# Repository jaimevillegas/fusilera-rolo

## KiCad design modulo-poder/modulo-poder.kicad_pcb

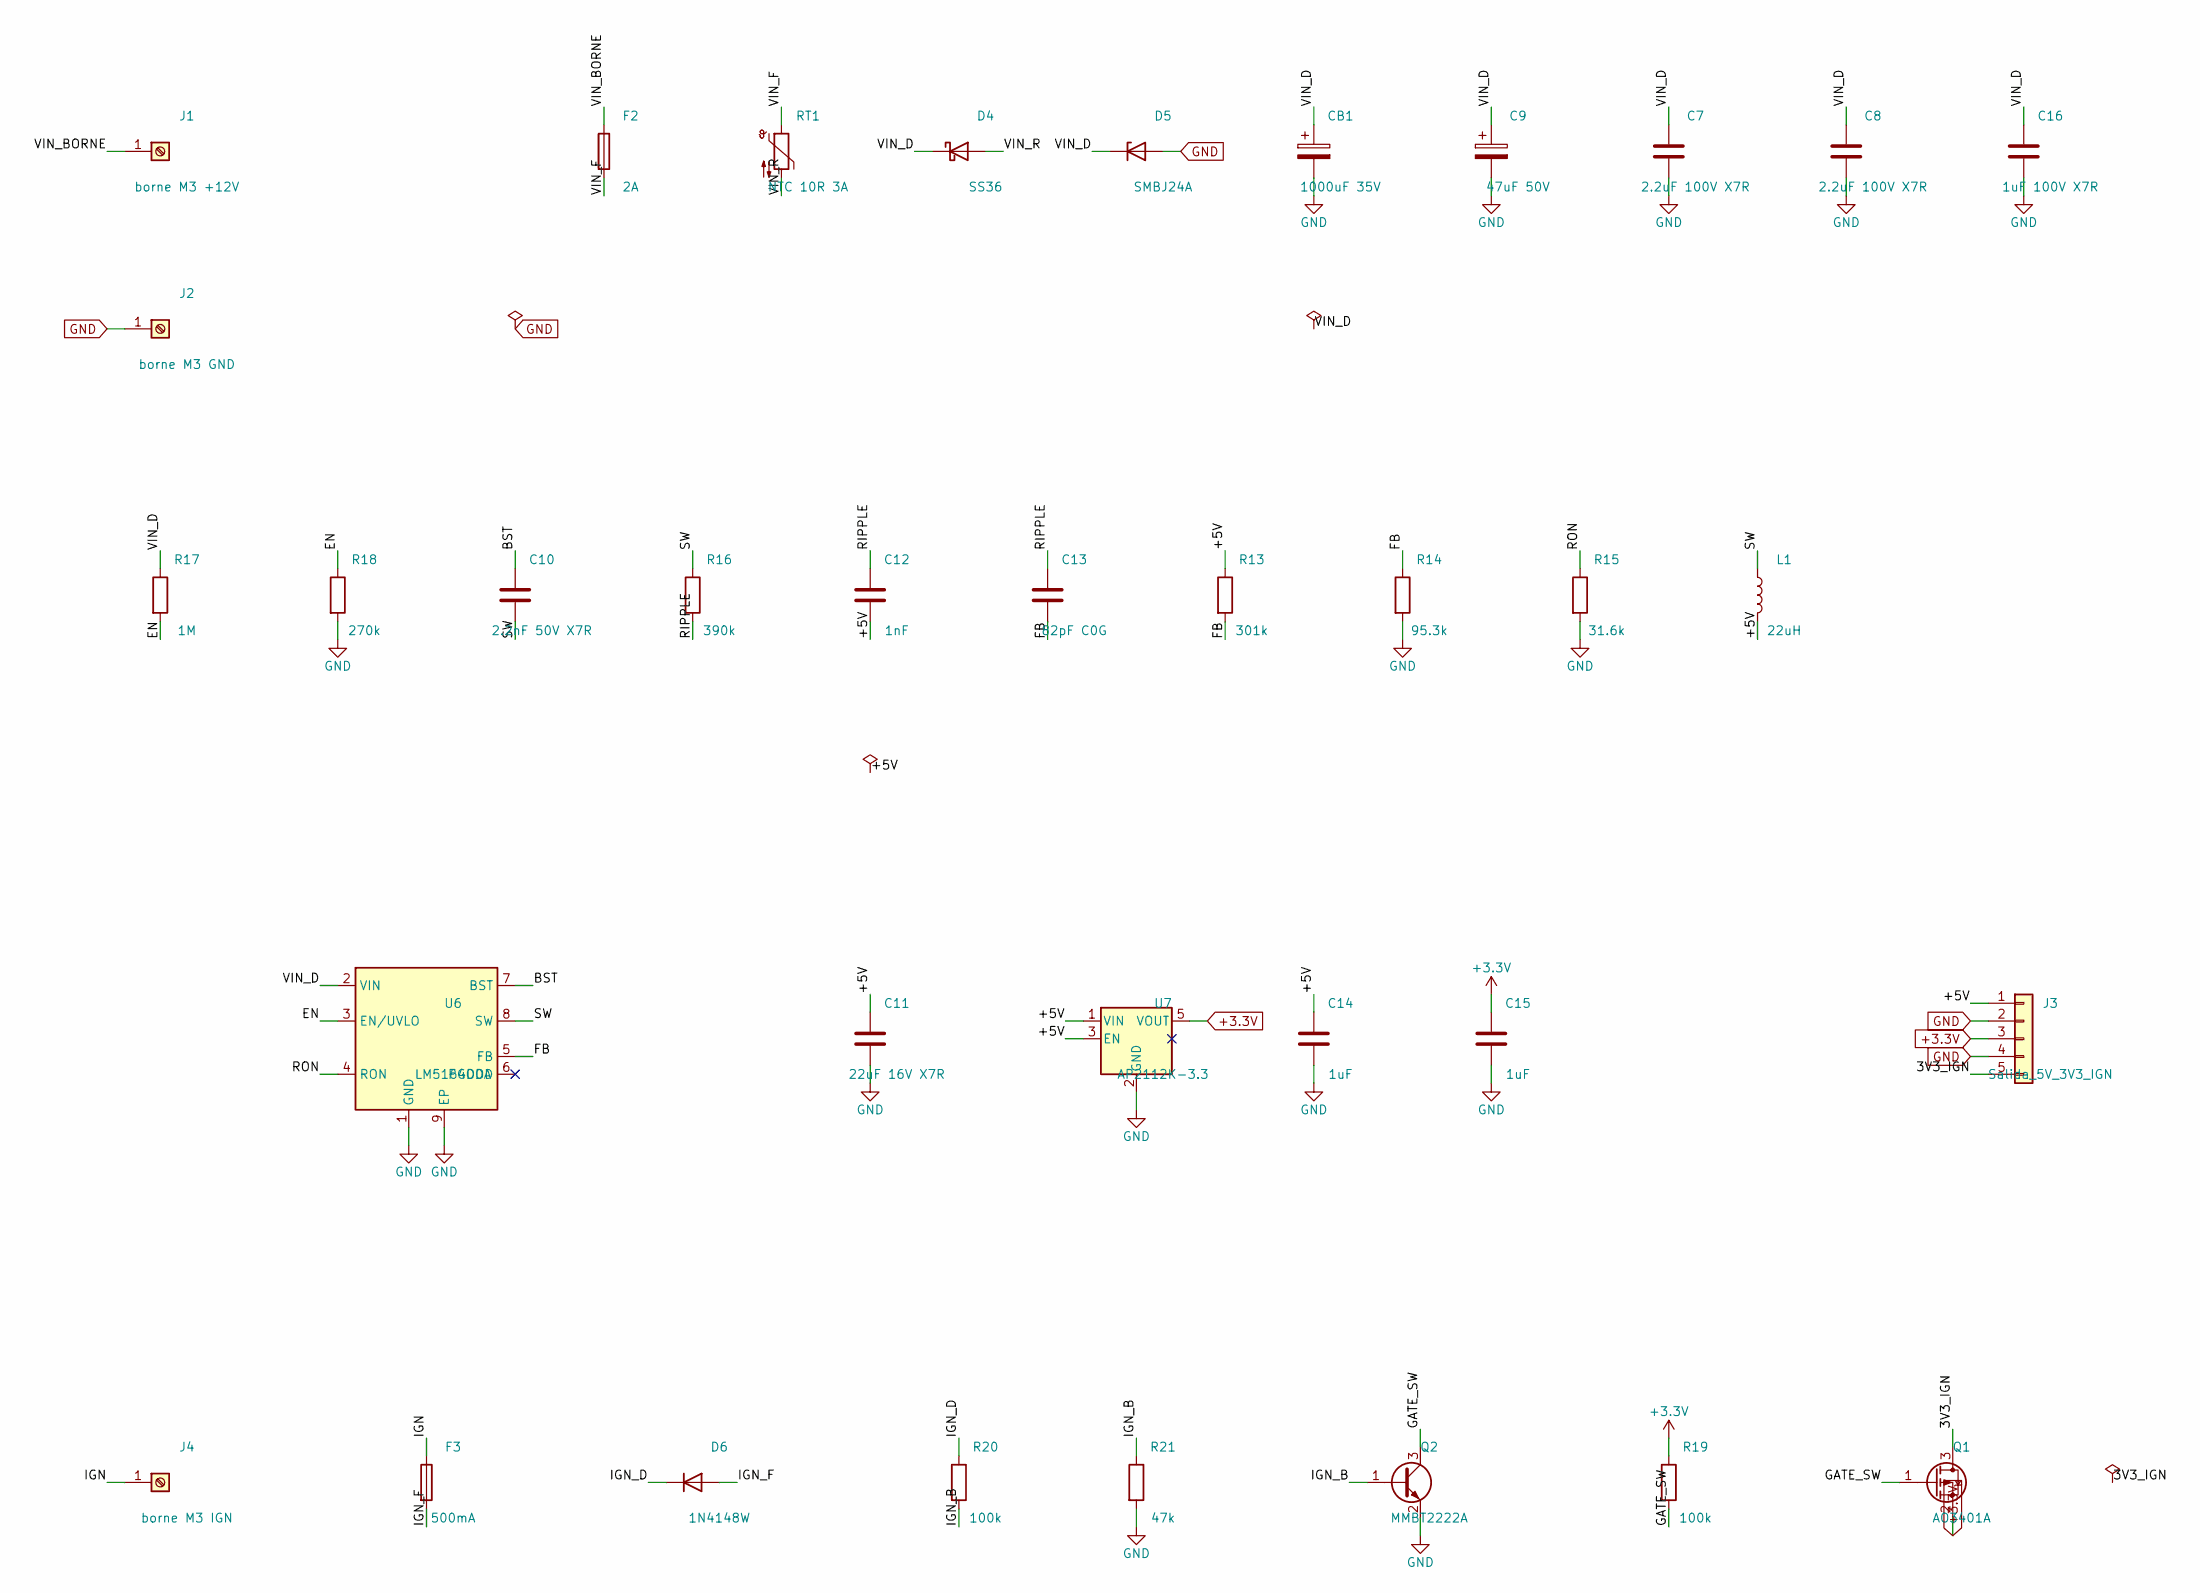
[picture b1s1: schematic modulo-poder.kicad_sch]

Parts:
C7, C8: 2.2uF 100V X7R; C_1210_3225Metric
C9: 47uF 50V; CP_Elec_8x10
C10: 2.2nF 50V X7R; C_0805_2012Metric
C11: 22uF 16V X7R; C_1206_3216Metric
C12: 1nF; C_0805_2012Metric
C13: 82pF C0G; C_0805_2012Metric
C14, C15: 1uF; C_0805_2012Metric
C16: 1uF 100V X7R; C_0805_2012Metric
CB1: 1000uF 35V; CP_Radial_D10.0mm_P5.00mm
D4: SS36; D_SMB
D5: SMBJ24A; D_SMB
D6: 1N4148W; D_SOD-123
F2: 2A; Fuse_1206_3216Metric
F3: 500mA; Fuse_1206_3216Metric
J1: borne M3 +12V; MountingHole_3.2mm_M3_Pad
J2: borne M3 GND; MountingHole_3.2mm_M3_Pad
J3: Salida_5V_3V3_IGN; JST_XH_B5B-XH-A_1x05_P2.50mm_Vertical
J4: borne M3 IGN; MountingHole_3.2mm_M3_Pad
L1: 22uH; L_6.3x6.3_H3
Q1: AO3401A; SOT-23
Q2: MMBT2222A; SOT-23
R13: 301k; R_0805_2012Metric
R14: 95.3k; R_0805_2012Metric
R15: 31.6k; R_0805_2012Metric
R16: 390k; R_0805_2012Metric
R17: 1M; R_0805_2012Metric
R18: 270k; R_0805_2012Metric
R19, R20: 100k; R_0805_2012Metric
R21: 47k; R_0805_2012Metric
RT1: NTC 10R 3A; RV_Disc_D9mm_W4.2mm_P5mm
U6: LM5164DDA; HSOP-8-1EP_3.9x4.9mm_P1.27mm_EP2.41x3.1mm
U7: AP2112K-3.3; SOT-23-5

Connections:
+3.3V: C15.1, J3.3, Q1.2 (S), R19.1, U7.5 (VOUT)
/3V3_IGN: J3.5, Q1.3 (D)
/+5V: C11.1, C12.2, C14.1, J3.1, L1.2, R13.1, U7.1 (VIN), U7.3 (EN)
/BST: C10.1, U6.7 (BST)
/EN: R17.2, R18.1, U6.3 (EN/UVLO)
/FB: C13.2, R13.2, R14.1, U6.5 (FB)
/GATE_SW: Q1.1 (G), Q2.3 (C), R19.2
/IGN: F3.1, J4.1; also elsewhere on the board
/IGN_B: Q2.1 (B), R20.2, R21.1
/IGN_D: D6.1 (K), R20.1
/IGN_F: D6.2 (A), F3.2
/RIPPLE: C12.1, C13.1, R16.2
/RON: R15.1, U6.4 (RON)
/SW: C10.2, L1.1, R16.1, U6.8 (SW)
/VIN_BORNE: F2.1, J1.1; also elsewhere on the board
/VIN_D: C7.1, C8.1, C9.1, C16.1, CB1.1, D4.1 (K), D5.1 (K), R17.1, U6.2 (VIN)
/VIN_F: F2.2, RT1.1
/VIN_R: D4.2 (A), RT1.2
GND: C7.2, C8.2, C9.2, C11.2, C14.2, C15.2, C16.2, CB1.2, D5.2 (A), J2.1, J3.2, J3.4, Q2.2 (E), R14.2, R15.2, R18.2, R21.2, U6.1 (GND), U6.9 (EP), U7.2 (GND); also elsewhere on the board

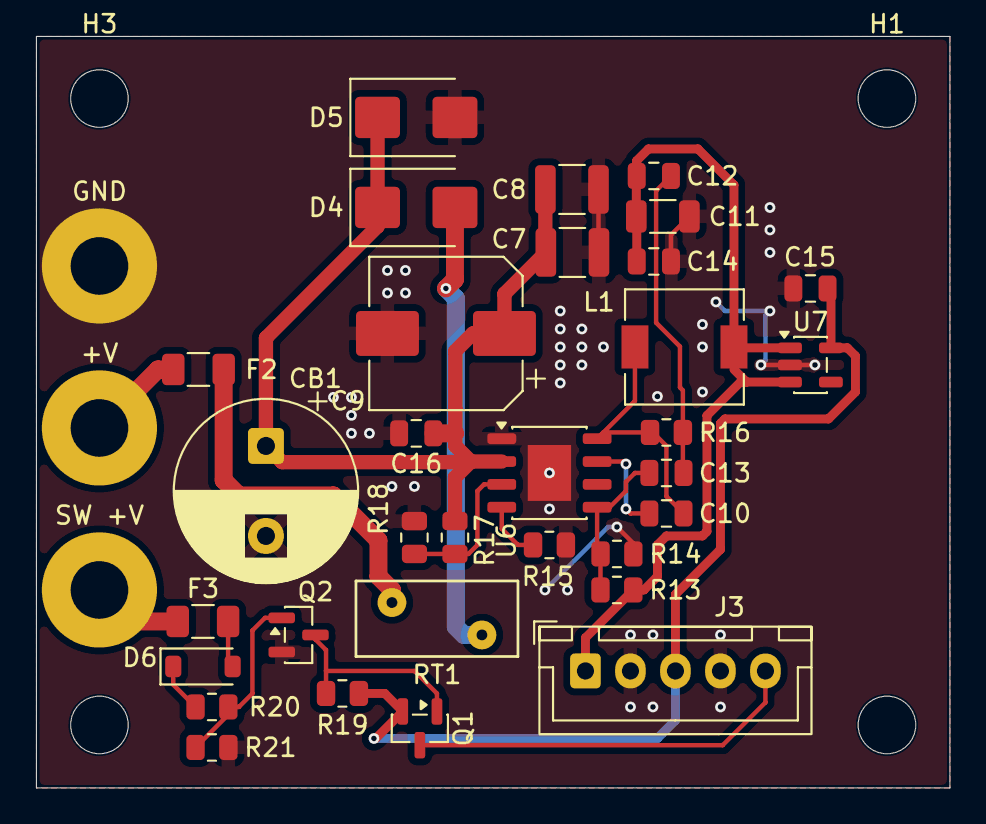
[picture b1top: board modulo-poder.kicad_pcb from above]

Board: 2 copper layers, 50.8 x 41.8 mm, 39 parts (0 on the bottom side), 19 nets.

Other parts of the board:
+V: borne M3 +12V; MountingHole_3.2mm_M3_Pad
GND: borne M3 GND; MountingHole_3.2mm_M3_Pad
H1, H2, H3, H4: MountingHole_3.2mm_M3
SW +V: borne M3 IGN; MountingHole_3.2mm_M3_Pad

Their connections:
/IGN: SW +V.1; also elsewhere on the board
/VIN_BORNE: +V.1; also elsewhere on the board
GND: GND.1; also elsewhere on the board

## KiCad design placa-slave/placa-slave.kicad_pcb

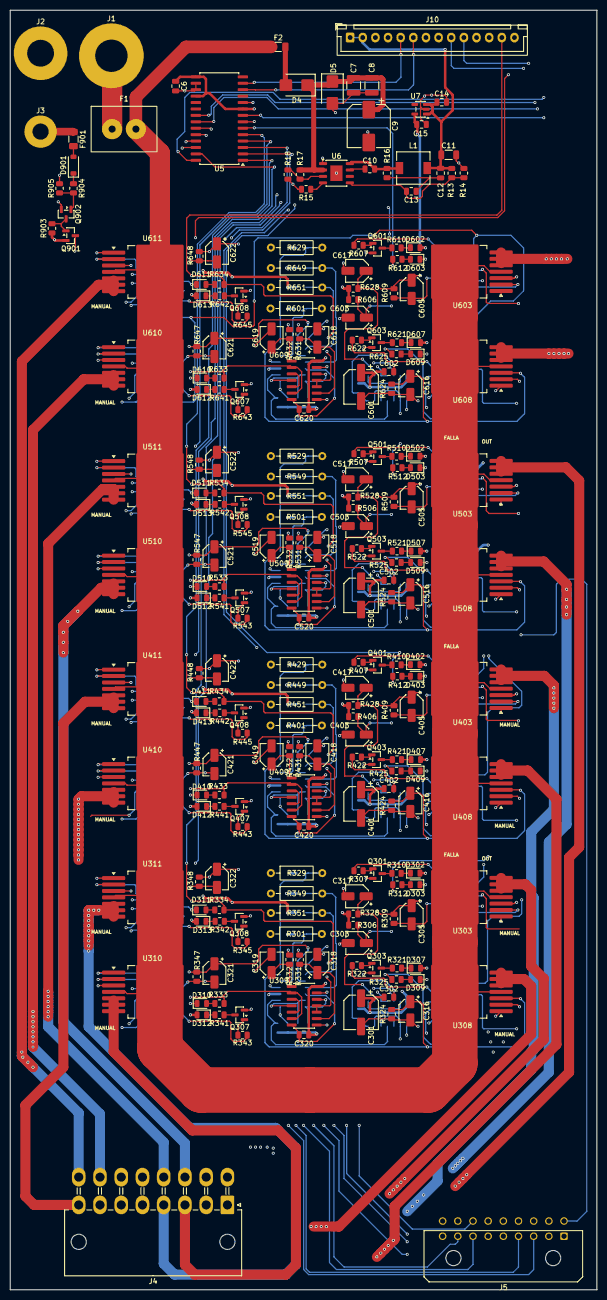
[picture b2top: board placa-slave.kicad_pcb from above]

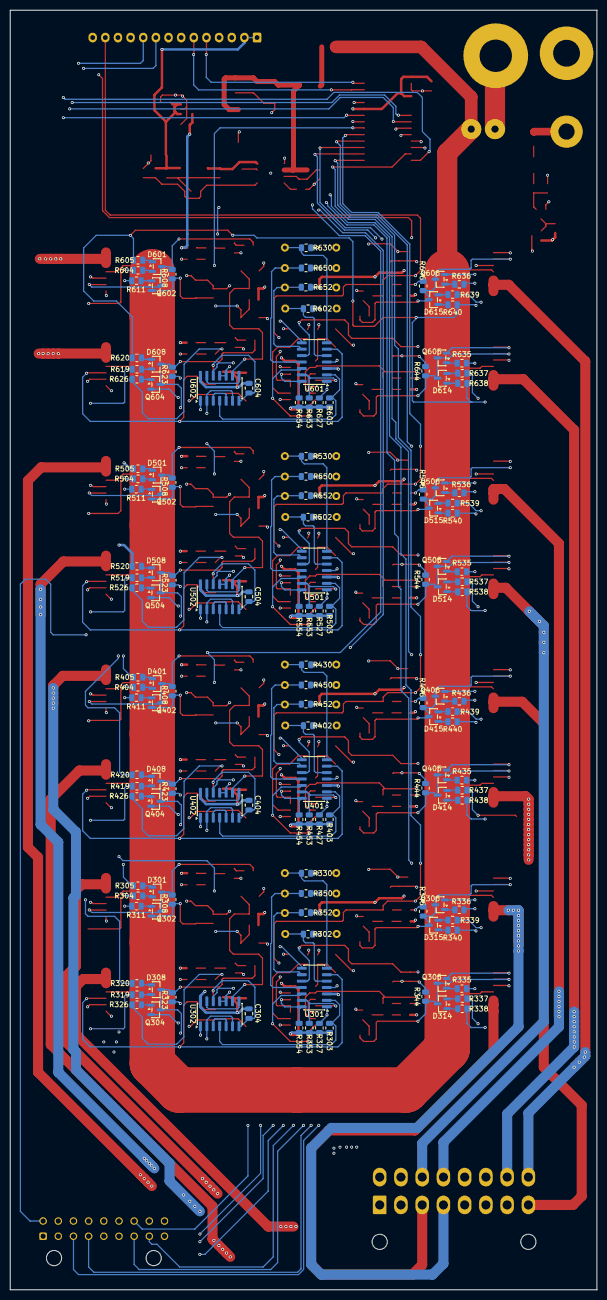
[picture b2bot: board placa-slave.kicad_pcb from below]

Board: 4 copper layers, 116.0 x 253.0 mm, 385 parts (140 on the bottom side), 284 nets.

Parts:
C6, C302, C304, C320, C402, C404, C420, C502, C504, C520, C602, C604, C620: 100nF; C_0805_2012Metric
C7, C8: 2.2uF 100V X7R; C_1210_3225Metric
C9: 47uF 50V; CP_Elec_8x10
C10: 2.2nF 50V X7R; C_0805_2012Metric
C11: 22uF 16V X7R; C_1206_3216Metric
C12: 1nF; C_0805_2012Metric
C13: 82pF C0G; C_0805_2012Metric
C14, C15: 1uF; C_0805_2012Metric
C301, C401, C501, C601: 100uF 16V; CP_Elec_6.3x5.4
C303, C305, C316, C317, C318, C319, C321, C322, C403, C405, C416, C417, C418, C419, C421, C422, C503, C505, C516, C517, C518, C519, C521, C522, C603, C605, C616, C617, C618, C619, C621, C622: 1uF 25V; CP_Elec_4x5.4
D4: SS36; D_SMB
D5: SMBJ; D_SMB
D301, D308, D314, D315, D401, D408, D414, D415, D501, D508, D514, D515, D601, D608, D614, D615: BAT54C; SOT-23
D302, D307, D312, D313, D402, D407, D412, D413, D502, D507, D512, D513, D602, D607, D612, D613: LED verde; LED_0805_2012Metric
D303, D309, D310, D311, D403, D409, D410, D411, D503, D509, D510, D511, D603, D609, D610, D611: LED rojo; LED_0805_2012Metric
D901: 1N4148W; D_SOD-123
F1: Portafusibles 40A; FuseHolder_2xFaston187_P4.70mm
F2: 2A; Fuse_1206_3216Metric
F901: 500mA; Fuse_1206_3216Metric
J1: +12V borne M6; MountingHole_6.4mm_M6_Pad
J2: GND borne M5; MountingHole_5.3mm_M5_Pad
J3: borne M3 IGN; MountingHole_3.2mm_M3_Pad
J4: Salidas_BTS; Molex_Mini-Fit_Jr_5569-16A2_2x08_P4.20mm_Horizontal
J5: Manuales; Molex_Micro-Fit_3.0_43045-1800_2x09_P3.00mm_Horizontal
J10: Enlace_placas; JST_XH_B14B-XH-A_1x14_P2.50mm_Vertical
L1: 22uH; L_6.3x6.3_H3
Q301, Q302, Q303, Q304, Q305, Q306, Q307, Q308, Q401, Q402, Q403, Q404, Q405, Q406, Q407, Q408, Q501, Q502, Q503, Q504, Q505, Q506, Q507, Q508, Q601, Q602, Q603, Q604, Q605, Q606, Q607, Q608, Q902: MMBT2222A; SOT-23
Q901: AO3401A; SOT-23
R13: 301k; R_0805_2012Metric
R14: 95.3k; R_0805_2012Metric
R15: 31.6k; R_0805_2012Metric
R16: 390k; R_0805_2012Metric
R17: 1M; R_0805_2012Metric
R18: 270k; R_0805_2012Metric
R301, R329, R349, R351, R401, R429, R449, R451, R501, R529, R549, R551, R601, R629, R649, R651: umbral; R_Axial_DIN0207_L6.3mm_D2.5mm_P10.16mm_Horizontal
R302, R303, R306, R327, R328, R330, R331, R332, R350, R352, R353, R354, R402, R403, R406, R427, R428, R430, R431, R432, R450, R452, R453, R454, R502, R503, R506, R527, R528, R530, R531, R532, R550, R552, R553, R554, R602, R603, R606, R627, R628, R630, R631, R632, R650, R652, R653, R654: 10k; R_0805_2012Metric
R304, R305, R311, R319, R320, R326, R335, R336, R337, R338, R339, R340, R404, R405, R411, R419, R420, R426, R435, R436, R437, R438, R439, R440, R504, R505, R511, R519, R520, R526, R535, R536, R537, R538, R539, R540, R604, R605, R611, R619, R620, R626, R635, R636, R637, R638, R639, R640: 4.7k; R_0805_2012Metric
R307, R308, R322, R323, R343, R344, R345, R346, R407, R408, R422, R423, R443, R444, R445, R446, R507, R508, R522, R523, R543, R544, R545, R546, R607, R608, R622, R623, R643, R644, R645, R646, R903, R904: 100k; R_0805_2012Metric
R309, R312, R324, R325, R333, R334, R347, R348, R409, R412, R424, R425, R433, R434, R447, R448, R509, R512, R524, R525, R533, R534, R547, R548, R609, R612, R624, R625, R633, R634, R647, R648: 1k; R_0805_2012Metric
R310, R321, R341, R342, R410, R421, R441, R442, R510, R521, R541, R542, R610, R621, R641, R642: 2.2k; R_0805_2012Metric
R905: 47k; R_0805_2012Metric
U5: MCP23017-E/SO; SOIC-28W_7.5x17.9mm_P1.27mm
U6: LM5164DDA; HSOP-8-1EP_3.9x4.9mm_P1.27mm_EP2.41x3.1mm
U7: AP2112K-3.3; SOT-23-5
U301, U401, U501, U601: LM339D; SOIC-14_3.9x8.7mm_P1.27mm
U302, U309, U402, U409, U502, U509, U602, U609: 74HC132D; SOIC-14_3.9x8.7mm_P1.27mm
U303, U308, U310, U311, U403, U408, U410, U411, U503, U508, U510, U511, U603, U608, U610, U611: BTS50010-1TAD; TO-263-7_TabPin4

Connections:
+3.3V: C6.1, C15.1, C301.1, C302.1, C304.1, C320.1, C401.1, C402.1, C404.1, C420.1, C501.1, C502.1, C504.1, C520.1, C601.1, C602.1, C604.1, C620.1, D302.2 (A), D307.2 (A), D312.2 (A), D313.2 (A), D402.2 (A), D407.2 (A), D412.2 (A), D413.2 (A), D502.2 (A), D507.2 (A), D512.2 (A), D513.2 (A), D602.2 (A), D607.2 (A), D612.2 (A), D613.2 (A), J5.17, Q901.2, R302.1, R303.2, R306.2, R327.2, R328.2, R330.1, R331.2, R332.2, R350.1, R352.1, R353.2, R354.2, R402.1, R403.2, R406.2, R427.2, R428.2, R430.1, R431.2, R432.2, R440.2, R450.1, R452.1, R453.2, R454.2, R502.1, R503.2, R505.2, R506.2, R520.2, R527.2, R528.2, R530.1, R531.2, R532.2, R538.2, R540.2, R550.1, R552.1, R553.2, R554.2, R602.1, R603.2, R606.2, R627.2, R628.2, R630.1, R631.2, R632.2, R650.1, R652.1, R653.2, R654.2, R903.1, U5.9, U5.15, U5.18, U7.5, U301.3 (V+), U302.14 (VCC), U309.14 (VCC), U401.3 (V+), U402.14 (VCC), U409.14 (VCC), U501.3 (V+), U502.14 (VCC), U509.14 (VCC), U601.3 (V+), U602.14 (VCC), U609.14 (VCC)
+12V: F1.2, F2.1, U303.4 (Vbb), U308.4 (Vbb), U310.4 (Vbb), U311.4 (Vbb), U403.4 (Vbb), U408.4 (Vbb), U410.4 (Vbb), U411.4 (Vbb), U503.4 (Vbb), U508.4 (Vbb), U510.4 (Vbb), U511.4 (Vbb), U603.4 (Vbb), U608.4 (Vbb), U610.4 (Vbb), U611.4 (Vbb)
/3V3_IGN: Q901.3, R605.2, R620.2, R638.2, R640.2
/ESP32_OUT13: R305.2, U5.28
/ESP32_OUT14: R320.2, U5.8
/ESP32_OUT15: J10.7, R338.2
/ESP32_OUT16: J10.8, R340.2
/ESP32_OUT17: J10.9, R405.2
/ESP32_OUT18: J10.10, R420.2
/ESP32_OUT19: J10.11, R438.2
/FALLA13: R311.2, R312.1, U5.21, U302.2, U302.6
/FALLA14: R325.1, R326.2, U5.22, U302.10, U302.11
/FALLA15: R333.1, R335.2, U5.23, U309.2, U309.6
/FALLA16: R334.1, R336.2, U5.24, U309.10, U309.11
/FALLA17: R411.2, R412.1, U5.25, U402.2, U402.6
/FALLA18: R425.1, R426.2, U5.26, U402.10, U402.11
/FALLA19: R433.1, R435.2, U5.27, U409.2, U409.6
/FALLA20: R434.1, R436.2, U5.1, U409.10, U409.11
/FALLA21: R511.2, R512.1, U5.2, U502.2, U502.6
/FALLA22: R525.1, R526.2, U5.3, U502.10, U502.11
/FALLA23: R533.1, R535.2, U5.4, U509.2, U509.6
/FALLA24: R534.1, R536.2, U5.5, U509.10, U509.11
/FALLA25: R611.2, R612.1, U5.6, U602.2, U602.6
/FALLA26: R625.1, R626.2, U5.7, U602.10, U602.11
/FALLA27: J10.12, R633.1, R635.2, U609.2, U609.6
/FALLA28: J10.13, R634.1, R636.2, U609.10, U609.11
/GATE_SW: Q901.1, Q902.3, R903.2
/IGN: F901.1, J3.1
/IGN_B: Q902.1, R904.2, R905.1
/IGN_D: D901.1, R904.1
/IGN_F: D901.2, F901.2
/LINK_5V: C11.1, C12.2, C14.1, J10.1, J10.2, L1.2, R13.1, U7.1, U7.3
/MANUAL13: J5.1, R304.1
/MANUAL14: J5.2, R319.1
/MANUAL15: J5.3, R337.1
/MANUAL16: J5.4, R339.1
/MANUAL17: J5.5, R404.1
/MANUAL18: J5.6, R419.1
/MANUAL19: J5.7, R437.1
/MANUAL20: J5.8, R439.1
/MANUAL21: J5.9, R504.1
/MANUAL22: J5.10, R519.1
/MANUAL23: J5.11, R537.1
/MANUAL24: J5.12, R539.1
/MANUAL25: J5.13, R604.1
/MANUAL26: J5.14, R619.1
/MANUAL27: J5.15, R637.1
/MANUAL28: J5.16, R639.1
/OUT13: J4.1, U303.5 (OUT), U303.6 (OUT), U303.7 (OUT)
/OUT14: J4.2, U308.5 (OUT), U308.6 (OUT), U308.7 (OUT)
/OUT15: J4.3, U310.5 (OUT), U310.6 (OUT), U310.7 (OUT)
/OUT16: J4.4, U311.5 (OUT), U311.6 (OUT), U311.7 (OUT)
/OUT17: J4.5, U403.5 (OUT), U403.6 (OUT), U403.7 (OUT)
/OUT18: J4.6, U408.5 (OUT), U408.6 (OUT), U408.7 (OUT)
/OUT19: J4.7, U410.5 (OUT), U410.6 (OUT), U410.7 (OUT)
/OUT20: J4.8, U411.5 (OUT), U411.6 (OUT), U411.7 (OUT)
/OUT21: J4.9, U503.5 (OUT), U503.6 (OUT), U503.7 (OUT)
/OUT22: J4.10, U508.5 (OUT), U508.6 (OUT), U508.7 (OUT)
/OUT23: J4.11, U510.5 (OUT), U510.6 (OUT), U510.7 (OUT)
/OUT24: J4.12, U511.5 (OUT), U511.6 (OUT), U511.7 (OUT)
/OUT25: J4.13, U603.5 (OUT), U603.6 (OUT), U603.7 (OUT)
/OUT26: J4.14, U608.5 (OUT), U608.6 (OUT), U608.7 (OUT)
/OUT27: J4.15, U610.5 (OUT), U610.6 (OUT), U610.7 (OUT)
/OUT28: J4.16, U611.5 (OUT), U611.6 (OUT), U611.7 (OUT)
/SCL: J10.6, U5.12
/SDA: J10.5, U5.13
/VIN_BORNE: F1.1, J1.1
GND: C6.2, C7.2, C8.2, C9.2, C11.2, C14.2, C15.2, C301.2, C302.2, C303.2, C304.2, C305.2, C316.2, C317.2, C318.2, C319.2, C320.2, C321.2, C322.2, C401.2, C402.2, C403.2, C404.2, C405.2, C416.2, C417.2, C418.2, C419.2, C420.2, C421.2, C422.2, C501.2, C502.2, C503.2, C504.2, C505.2, C516.2, C517.2, C518.2, C519.2, C520.2, C521.2, C522.2, C601.2, C602.2, C603.2, C604.2, C605.2, C616.2, C617.2, C618.2, C619.2, C620.2, C621.2, C622.2, D5.2, D303.1 (K), D309.1 (K), D310.1 (K), D311.1 (K), D403.1 (K), D409.1 (K), D410.1 (K), D411.1 (K), D503.1 (K), D509.1 (K), D510.1 (K), D511.1 (K), D603.1 (K), D609.1 (K), D610.1 (K), D611.1 (K), J2.1, J5.18, J10.3, J10.4, Q301.2 (E), Q302.2 (E), Q303.2 (E), Q304.2 (E), Q305.2 (E), Q306.2 (E), Q307.2 (E), Q308.2 (E), Q401.2 (E), Q402.2 (E), Q403.2 (E), Q404.2 (E), Q405.2 (E), Q406.2 (E), Q407.2 (E), Q408.2 (E), Q501.2 (E), Q502.2 (E), Q503.2 (E), Q504.2 (E), Q505.2 (E), Q506.2 (E), Q507.2 (E), Q508.2 (E), Q601.2 (E), Q602.2 (E), Q603.2 (E), Q604.2 (E), Q605.2 (E), Q606.2 (E), Q607.2 (E), Q608.2 (E), Q902.2, R14.2, R15.2, R18.2, R301.1, R308.2, R309.2, R323.2, R324.2, R329.1, R344.2, R346.2, R347.2, R348.2, R349.1, R351.1, R401.1, R408.2, R409.2, R423.2, R424.2, R429.1, R444.2, R446.2, R447.2, R448.2, R449.1, R451.1, R501.1, R508.2, R509.2, R523.2, R524.2, R529.1, R544.2, R546.2, R547.2, R548.2, R549.1, R551.1, R601.1, R608.2, R609.2, R623.2, R624.2, R629.1, R644.2, R646.2, R647.2, R648.2, R649.1, R651.1, R905.2, U5.10, U5.16, U5.17, U6.1, U6.9, U7.2, U301.12 (V-), U302.7 (GND), U303.1 (GND), U308.1 (GND), U309.7 (GND), U310.1 (GND), U311.1 (GND), U401.12 (V-), U402.7 (GND), U403.1 (GND), U408.1 (GND), U409.7 (GND), U410.1 (GND), U411.1 (GND), U501.12 (V-), U502.7 (GND), U503.1 (GND), U508.1 (GND), U509.7 (GND), U510.1 (GND), U511.1 (GND), U601.12 (V-), U602.7 (GND), U603.1 (GND), U608.1 (GND), U609.7 (GND), U610.1 (GND), U611.1 (GND)
unnamed: C12.1, C13.1, R16.2
unnamed: C303.1, R306.1, U302.1
unnamed: C317.1, R328.1, U302.9
unnamed: C318.1, R331.1, U309.9
unnamed: C319.1, R332.1, U309.1
unnamed: C403.1, R406.1, U402.1
unnamed: C417.1, R428.1, U402.9
unnamed: C418.1, R431.1, U409.9
unnamed: C419.1, R432.1, U409.1
unnamed: C503.1, R506.1, U502.1
unnamed: C517.1, R528.1, U502.9
unnamed: C518.1, R531.1, U509.9
unnamed: C519.1, R532.1, U509.1
unnamed: C603.1, R606.1, U602.1
unnamed: C617.1, R628.1, U602.9
unnamed: C618.1, R631.1, U609.9
unnamed: C619.1, R632.1, U609.1
unnamed: D4.2, F2.2
unnamed: C7.1, C8.1, C9.1, D4.1, D5.1, R17.1, U6.2
unnamed: D301.1, R305.1
unnamed: D301.2, R304.2
unnamed: D302.1 (K), R310.2
unnamed: D303.2 (A), R312.2
unnamed: D307.1 (K), R321.2
unnamed: D308.1, R320.1
unnamed: D308.2, R319.2
unnamed: D309.2 (A), R325.2
unnamed: D310.2 (A), R333.2
unnamed: D311.2 (A), R334.2
unnamed: D312.1 (K), R341.2
unnamed: D313.1 (K), R342.2
unnamed: D314.1, R338.1
unnamed: D314.2, R337.2
unnamed: D315.1, R340.1
unnamed: D315.2, R339.2
unnamed: D401.1, R405.1
unnamed: D401.2, R404.2
unnamed: D402.1 (K), R410.2
unnamed: D403.2 (A), R412.2
unnamed: D407.1 (K), R421.2
unnamed: D408.1, R420.1
unnamed: D408.2, R419.2
unnamed: D409.2 (A), R425.2
unnamed: D410.2 (A), R433.2
unnamed: D411.2 (A), R434.2
unnamed: D412.1 (K), R441.2
unnamed: D413.1 (K), R442.2
unnamed: D414.1, R438.1
unnamed: D414.2, R437.2
unnamed: D415.1, R440.1
unnamed: D415.2, R439.2
unnamed: D501.1, R505.1
unnamed: D501.2, R504.2
unnamed: D502.1 (K), R510.2
unnamed: D503.2 (A), R512.2
unnamed: D507.1 (K), R521.2
unnamed: D508.1, R520.1
unnamed: D508.2, R519.2
unnamed: D509.2 (A), R525.2
unnamed: D510.2 (A), R533.2
unnamed: D511.2 (A), R534.2
unnamed: D512.1 (K), R541.2
unnamed: D513.1 (K), R542.2
unnamed: D514.1, R538.1
unnamed: D514.2, R537.2
unnamed: D515.1, R540.1
unnamed: D515.2, R539.2
unnamed: D601.1, R605.1
unnamed: D601.2, R604.2
unnamed: D602.1 (K), R610.2
unnamed: D603.2 (A), R612.2
unnamed: D607.1 (K), R621.2
unnamed: D608.1, R620.1
unnamed: D608.2, R619.2
unnamed: D609.2 (A), R625.2
unnamed: D610.2 (A), R633.2
unnamed: D611.2 (A), R634.2
unnamed: D612.1 (K), R641.2
unnamed: D613.1 (K), R642.2
unnamed: D614.1, R638.1
unnamed: D614.2, R637.2
unnamed: D615.1, R640.1
unnamed: D615.2, R639.2
unnamed: Q301.1 (B), R307.1
unnamed: Q301.3 (C), R310.1
unnamed: Q302.1 (B), R311.1
unnamed: D301.3, Q302.3 (C), R307.2, R308.1, U303.2 (IN)
unnamed: Q303.1 (B), R322.1
unnamed: Q303.3 (C), R321.1
unnamed: Q304.1 (B), R326.1
unnamed: D308.3, Q304.3 (C), R322.2, R323.1, U308.2 (IN)
unnamed: Q305.1 (B), R335.1
unnamed: D314.3, Q305.3 (C), R343.2, R344.1, U310.2 (IN)
unnamed: Q306.1 (B), R336.1
unnamed: D315.3, Q306.3 (C), R345.2, R346.1, U311.2 (IN)
unnamed: Q307.1 (B), R343.1
unnamed: Q307.3 (C), R341.1
unnamed: Q308.1 (B), R345.1
unnamed: Q308.3 (C), R342.1
unnamed: Q401.1 (B), R407.1
unnamed: Q401.3 (C), R410.1
unnamed: Q402.1 (B), R411.1
unnamed: D401.3, Q402.3 (C), R407.2, R408.1, U403.2 (IN)
unnamed: Q403.1 (B), R422.1
unnamed: Q403.3 (C), R421.1
unnamed: Q404.1 (B), R426.1
unnamed: D408.3, Q404.3 (C), R422.2, R423.1, U408.2 (IN)
unnamed: Q405.1 (B), R435.1
unnamed: D414.3, Q405.3 (C), R443.2, R444.1, U410.2 (IN)
unnamed: Q406.1 (B), R436.1
unnamed: D415.3, Q406.3 (C), R445.2, R446.1, U411.2 (IN)
unnamed: Q407.1 (B), R443.1
unnamed: Q407.3 (C), R441.1
unnamed: Q408.1 (B), R445.1
unnamed: Q408.3 (C), R442.1
unnamed: Q501.1 (B), R507.1
unnamed: Q501.3 (C), R510.1
unnamed: Q502.1 (B), R511.1
unnamed: D501.3, Q502.3 (C), R507.2, R508.1, U503.2 (IN)
unnamed: Q503.1 (B), R522.1
unnamed: Q503.3 (C), R521.1
unnamed: Q504.1 (B), R526.1
unnamed: D508.3, Q504.3 (C), R522.2, R523.1, U508.2 (IN)
unnamed: Q505.1 (B), R535.1
unnamed: D514.3, Q505.3 (C), R543.2, R544.1, U510.2 (IN)
unnamed: Q506.1 (B), R536.1
unnamed: D515.3, Q506.3 (C), R545.2, R546.1, U511.2 (IN)
unnamed: Q507.1 (B), R543.1
unnamed: Q507.3 (C), R541.1
unnamed: Q508.1 (B), R545.1
unnamed: Q508.3 (C), R542.1
unnamed: Q601.1 (B), R607.1
unnamed: Q601.3 (C), R610.1
unnamed: Q602.1 (B), R611.1
unnamed: D601.3, Q602.3 (C), R607.2, R608.1, U603.2 (IN)
unnamed: Q603.1 (B), R622.1
unnamed: Q603.3 (C), R621.1
unnamed: Q604.1 (B), R626.1
unnamed: D608.3, Q604.3 (C), R622.2, R623.1, U608.2 (IN)
unnamed: Q605.1 (B), R635.1
unnamed: D614.3, Q605.3 (C), R643.2, R644.1, U610.2 (IN)
unnamed: Q606.1 (B), R636.1
unnamed: D615.3, Q606.3 (C), R645.2, R646.1, U611.2 (IN)
unnamed: Q607.1 (B), R643.1
unnamed: Q607.3 (C), R641.1
unnamed: Q608.1 (B), R645.1
unnamed: Q608.3 (C), R642.1
unnamed: R303.1, U301.2, U302.4
unnamed: R327.1, U301.1, U302.12
unnamed: R353.1, U301.13, U309.4
unnamed: R354.1, U301.14, U309.12
unnamed: R403.1, U401.2, U402.4
unnamed: R427.1, U401.1, U402.12
unnamed: R453.1, U401.13, U409.4
unnamed: R454.1, U401.14, U409.12
unnamed: R503.1, U501.2, U502.4
unnamed: R527.1, U501.1, U502.12
unnamed: R553.1, U501.13, U509.4
unnamed: R554.1, U501.14, U509.12
unnamed: R603.1, U601.2, U602.4
unnamed: R627.1, U601.1, U602.12
unnamed: R653.1, U601.13, U609.4
unnamed: R654.1, U601.14, U609.12
unnamed: C10.1, U6.7
unnamed: R17.2, R18.1, U6.3
unnamed: C13.2, R13.2, R14.1, U6.5
unnamed: R15.1, U6.4
unnamed: C10.2, L1.1, R16.1, U6.8
unnamed: R301.2, R302.2, U301.5 (+)
unnamed: C305.1, R309.1, U301.4 (-), U303.3 (IS)
unnamed: R329.2, R330.2, U301.7 (+)
unnamed: C316.1, R324.1, U301.6 (-), U308.3 (IS)
unnamed: R349.2, R350.2, U301.11 (+)
unnamed: C321.1, R347.1, U301.10 (-), U310.3 (IS)
unnamed: R351.2, R352.2, U301.9 (+)
unnamed: C322.1, R348.1, U301.8 (-), U311.3 (IS)
unnamed: U302.3, U302.5
unnamed: U302.8, U302.13
unnamed: U309.3, U309.5
unnamed: U309.8, U309.13
unnamed: R401.2, R402.2, U401.5 (+)
unnamed: C405.1, R409.1, U401.4 (-), U403.3 (IS)
unnamed: R429.2, R430.2, U401.7 (+)
unnamed: C416.1, R424.1, U401.6 (-), U408.3 (IS)
unnamed: R449.2, R450.2, U401.11 (+)
unnamed: C421.1, R447.1, U401.10 (-), U410.3 (IS)
unnamed: R451.2, R452.2, U401.9 (+)
unnamed: C422.1, R448.1, U401.8 (-), U411.3 (IS)
unnamed: U402.3, U402.5
unnamed: U402.8, U402.13
unnamed: U409.3, U409.5
unnamed: U409.8, U409.13
unnamed: R501.2, R502.2, U501.5 (+)
unnamed: C505.1, R509.1, U501.4 (-), U503.3 (IS)
unnamed: R529.2, R530.2, U501.7 (+)
unnamed: C516.1, R524.1, U501.6 (-), U508.3 (IS)
unnamed: R549.2, R550.2, U501.11 (+)
unnamed: C521.1, R547.1, U501.10 (-), U510.3 (IS)
unnamed: R551.2, R552.2, U501.9 (+)
unnamed: C522.1, R548.1, U501.8 (-), U511.3 (IS)
unnamed: U502.3, U502.5
unnamed: U502.8, U502.13
unnamed: U509.3, U509.5
unnamed: U509.8, U509.13
unnamed: R601.2, R602.2, U601.5 (+)
unnamed: C605.1, R609.1, U601.4 (-), U603.3 (IS)
unnamed: R629.2, R630.2, U601.7 (+)
unnamed: C616.1, R624.1, U601.6 (-), U608.3 (IS)
unnamed: R649.2, R650.2, U601.11 (+)
unnamed: C621.1, R647.1, U601.10 (-), U610.3 (IS)
unnamed: R651.2, R652.2, U601.9 (+)
unnamed: C622.1, R648.1, U601.8 (-), U611.3 (IS)
unnamed: U602.3, U602.5
unnamed: U602.8, U602.13
unnamed: U609.3, U609.5
unnamed: U609.8, U609.13

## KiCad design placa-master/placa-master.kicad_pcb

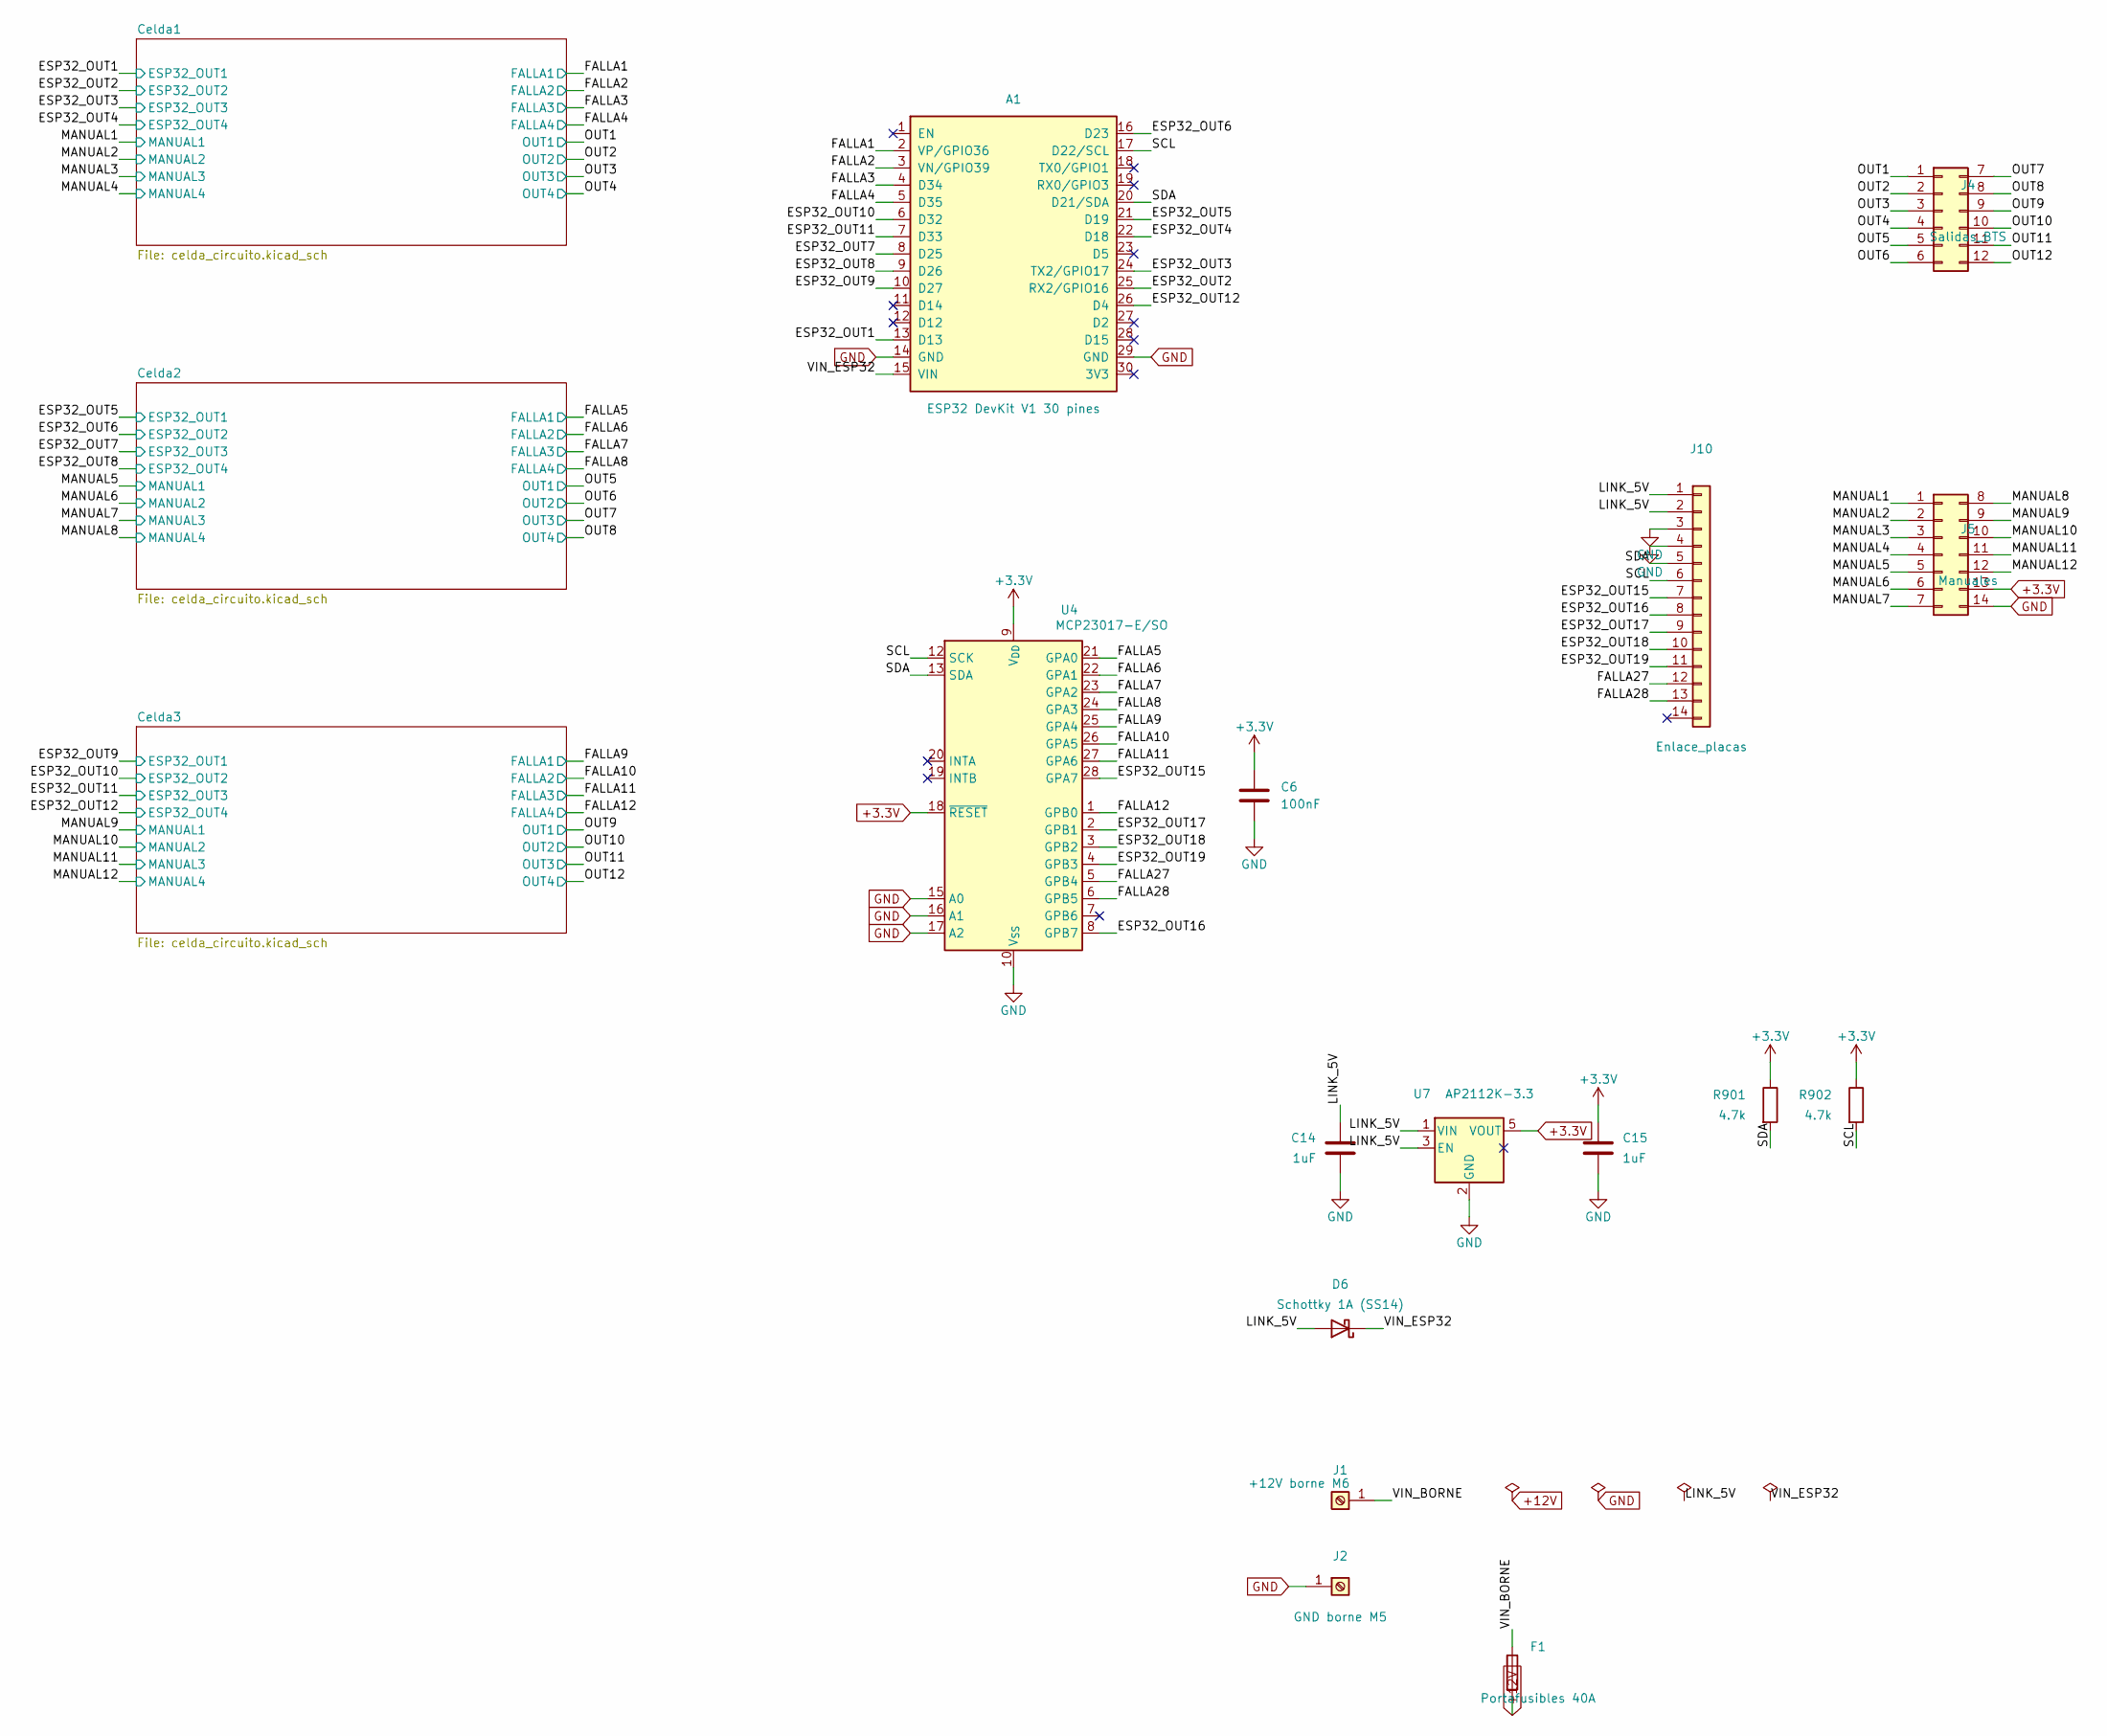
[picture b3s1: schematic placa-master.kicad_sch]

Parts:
A1: ESP32 DevKit V1 30 pines; ESP32_DevKit_30pin_Socket
C6: 100nF; C_0805_2012Metric
C14, C15: 1uF; C_0805_2012Metric
D6: Schottky 1A (SS14); D_SMA
F1: Portafusibles 40A; FuseHolder_2xFaston187_P4.70mm
J1: +12V borne M6; MountingHole_6.4mm_M6_Pad
J2: GND borne M5; MountingHole_5.3mm_M5_Pad
J4: Salidas_BTS; Molex_Mini-Fit_Jr_5569-12A2_2x06_P4.20mm_Horizontal
J5: Manuales; Molex_Micro-Fit_3.0_43045-1400_2x07_P3.00mm_Horizontal
J10: Enlace_placas; JST_XH_B14B-XH-A_1x14_P2.50mm_Vertical
R901, R902: 4.7k; R_0805_2012Metric
U4: MCP23017-E/SO; SOIC-28W_7.5x17.9mm_P1.27mm
U7: AP2112K-3.3; SOT-23-5

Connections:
+3.3V: C6.1, C15.1, J5.13, R901.1, R902.1, U4.9 (V_{DD}), U4.18 (~RESET), U7.5 (VOUT); also elsewhere on the board
+12V: F1.2; also elsewhere on the board
/ESP32_OUT1: A1.13 (D13); also elsewhere on the board
/ESP32_OUT2: A1.25 (RX2/GPIO16); also elsewhere on the board
/ESP32_OUT3: A1.24 (TX2/GPIO17); also elsewhere on the board
/ESP32_OUT4: A1.22 (D18); also elsewhere on the board
/ESP32_OUT5: A1.21 (D19); also elsewhere on the board
/ESP32_OUT6: A1.16 (D23); also elsewhere on the board
/ESP32_OUT7: A1.8 (D25); also elsewhere on the board
/ESP32_OUT8: A1.9 (D26); also elsewhere on the board
/ESP32_OUT9: A1.10 (D27); also elsewhere on the board
/ESP32_OUT10: A1.6 (D32); also elsewhere on the board
/ESP32_OUT11: A1.7 (D33); also elsewhere on the board
/ESP32_OUT12: A1.26 (D4); also elsewhere on the board
/ESP32_OUT15: J10.7, U4.28 (GPA7)
/ESP32_OUT16: J10.8, U4.8 (GPB7)
/ESP32_OUT17: J10.9, U4.2 (GPB1)
/ESP32_OUT18: J10.10, U4.3 (GPB2)
/ESP32_OUT19: J10.11, U4.4 (GPB3)
/FALLA1: A1.2 (VP/GPIO36); also elsewhere on the board
/FALLA2: A1.3 (VN/GPIO39); also elsewhere on the board
/FALLA3: A1.4 (D34); also elsewhere on the board
/FALLA4: A1.5 (D35); also elsewhere on the board
/FALLA5: U4.21 (GPA0); also elsewhere on the board
/FALLA6: U4.22 (GPA1); also elsewhere on the board
/FALLA7: U4.23 (GPA2); also elsewhere on the board
/FALLA8: U4.24 (GPA3); also elsewhere on the board
/FALLA9: U4.25 (GPA4); also elsewhere on the board
/FALLA10: U4.26 (GPA5); also elsewhere on the board
/FALLA11: U4.27 (GPA6); also elsewhere on the board
/FALLA12: U4.1 (GPB0); also elsewhere on the board
/FALLA27: J10.12, U4.5 (GPB4)
/FALLA28: J10.13, U4.6 (GPB5)
/LINK_5V: C14.1, D6.2 (A), J10.1, J10.2, U7.1 (VIN), U7.3 (EN)
/MANUAL1: J5.1; also elsewhere on the board
/MANUAL2: J5.2; also elsewhere on the board
/MANUAL3: J5.3; also elsewhere on the board
/MANUAL4: J5.4; also elsewhere on the board
/MANUAL5: J5.5; also elsewhere on the board
/MANUAL6: J5.6; also elsewhere on the board
/MANUAL7: J5.7; also elsewhere on the board
/MANUAL8: J5.8; also elsewhere on the board
/MANUAL9: J5.9; also elsewhere on the board
/MANUAL10: J5.10; also elsewhere on the board
/MANUAL11: J5.11; also elsewhere on the board
/MANUAL12: J5.12; also elsewhere on the board
/OUT1: J4.1; also elsewhere on the board
/OUT2: J4.2; also elsewhere on the board
/OUT3: J4.3; also elsewhere on the board
/OUT4: J4.4; also elsewhere on the board
/OUT5: J4.5; also elsewhere on the board
/OUT6: J4.6; also elsewhere on the board
/OUT7: J4.7; also elsewhere on the board
/OUT8: J4.8; also elsewhere on the board
/OUT9: J4.9; also elsewhere on the board
/OUT10: J4.10; also elsewhere on the board
/OUT11: J4.11; also elsewhere on the board
/OUT12: J4.12; also elsewhere on the board
/SCL: A1.17 (D22/SCL), J10.6, R902.2, U4.12 (SCK)
/SDA: A1.20 (D21/SDA), J10.5, R901.2, U4.13 (SDA)
/VIN_BORNE: F1.1, J1.1
/VIN_ESP32: A1.15 (VIN), D6.1 (K)
GND: A1.14 (GND), A1.29 (GND), C6.2, C14.2, C15.2, J2.1, J5.14, J10.3, J10.4, U4.10 (V_{SS}), U4.15 (A0), U4.16 (A1), U4.17 (A2), U7.2 (GND); also elsewhere on the board
